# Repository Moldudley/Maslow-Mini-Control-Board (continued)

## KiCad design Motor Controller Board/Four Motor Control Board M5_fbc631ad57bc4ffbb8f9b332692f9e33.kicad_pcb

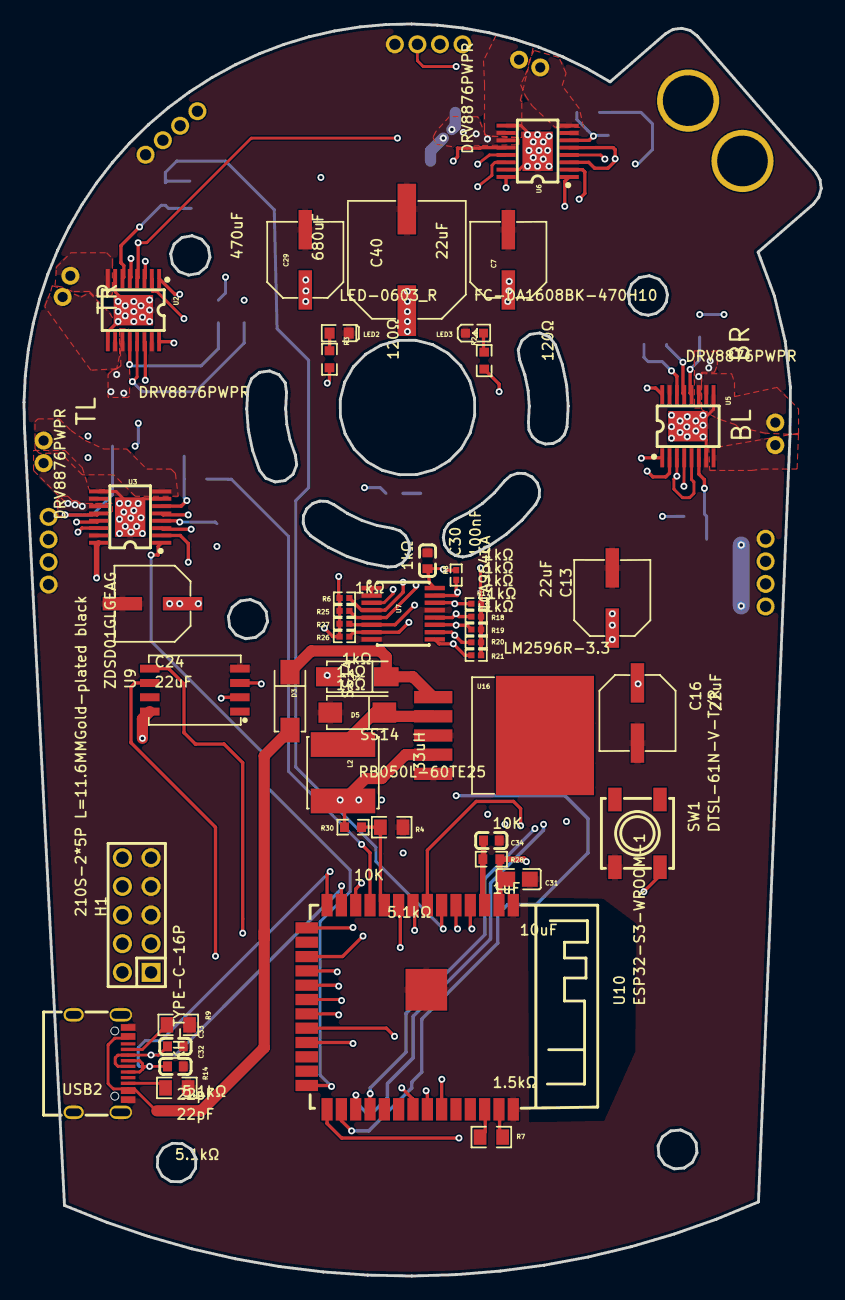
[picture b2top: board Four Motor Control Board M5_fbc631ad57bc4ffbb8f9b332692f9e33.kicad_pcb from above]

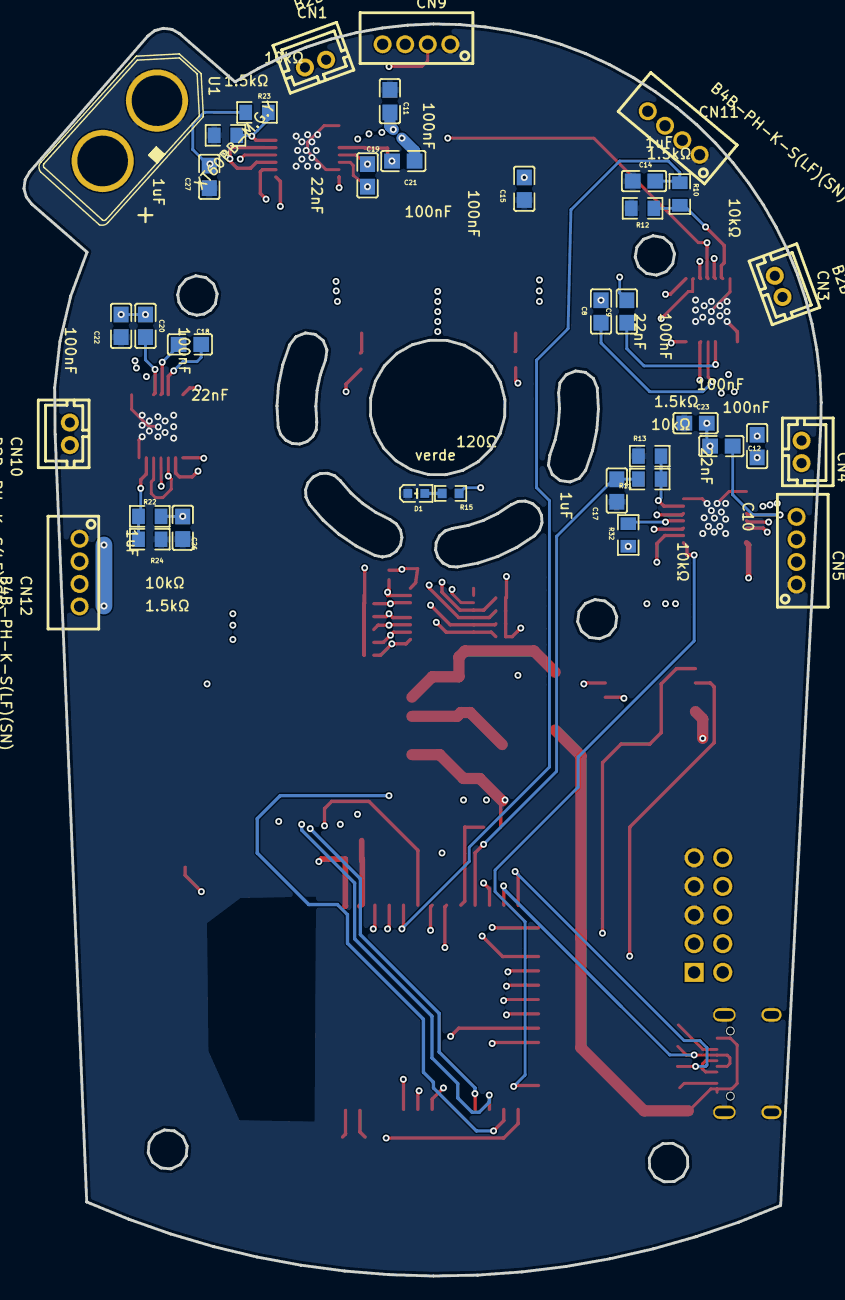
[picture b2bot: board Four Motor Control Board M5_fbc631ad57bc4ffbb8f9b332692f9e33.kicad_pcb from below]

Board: 4 copper layers, 70.7 x 111.0 mm, 82 parts (36 on the bottom side), 73 nets.

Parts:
C7, C13, C16, C24: 22uF; CAP-SMD_BD6.3-L6.6-W6.6-LS7.3-FD
C8, C10, C18, C19: 22nF; C0805
C9, C11, C12, C15, C20, C21, C22, C23: 100nF; C0805
C14, C17, C26, C27: 1uF; C0805
C29: 470uF; CAP-SMD_BD6.3-L6.6-W6.6-LS7.6-RD
C30: 100nF; C0603
C31: 10uF; C0805
C32, C33: 22pF; C0603
C34: 1uF; C0603
C40: 680uF; CAP-SMD_BD10.0-L10.3-W10.3-LS10.9-FD
CN1, CN3, CN4, CN10: B2B-PH-K-S(LF)(SN); CONN-TH_B2B-PH-K-S
CN5, CN9, CN11, CN12: B4B-PH-K-S(LF)(SN); CONN-TH_B4B-PH-K-S
D1: verde; LED0603-R-RD
D2, D3: SS14; SMA_L4.2-W2.6-LS5.3-RD
D5: RB050L-60TE25; SMA_L4.3-W2.7-LS5.1-RD
H1: 210S-2*5P L=11.6MMGold-plated black; HDR-TH_10P-P2.54-V-M-R2-C5-S2.54
L2: 33uH; IND-SMD_L6.0-W6.0
LED2: LED-0603_R; LED0603_RED
LED3: FC-DA1608BK-470H10; LED0603-RD
R1, R7, R12, R13, R24: 1.5kΩ; R0805
R2, R3, R15: 120Ω; R0603
R4, R9, R14: 5.1kΩ; R0805
R6, R8, R17, R18, R19, R20, R21, R25, R26, R27: 1kΩ; R0402
R10, R11, R22, R23, R32: 10kΩ; R0805
R28, R30: 10K; R0603
SW1: DTSL-61N-V-T/R; SW-SMD_4P-L6.2-W6.4-P4.00-LS7.2
U1: XT60PB-M.G.Y; CONN-TH_XT60PB-M
U2, U3, U5, U6: DRV8876PWPR; HTSSOP-16_L5.0-W4.4-P0.65-LS6.4-BL-EP
U7: TCA9546A; SOP-16_L5.0-W4.4-P0.65-LS6.4-BL
U9: ZDSD01GLGEAG; LGA-8_L6.0-W8.0-P1.27-BL
U10: ESP32-S3-WROOM-1
U16: LM2596R-3.3; TO-263-5_L10.2-W8.6-P1.70-LS14.4-TL
USB2: KH-TYPE-C-16P; USB-C-SMD_KH-TYPE-C-16P

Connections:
3V3: C29.1, C30.2, C31.2, CN5.4, CN9.4, CN11.4, CN12.4, L2.2, R6.2, R8.2, R15.2, R17.2, R18.2, R19.2, R20.2, R21.2, R25.2, R26.1, R27.2, R28.2, R30.2, R32.2, U2.3, U2.5, U2.16, U3.3, U3.5, U3.16, U5.3, U5.5, U5.16, U6.3, U6.5, U6.16, U7.3, U7.16, U9.8, U10.2, U16.4
ADCBL: C26.2, R22.1, U10.12
ADCBR: C27.2, R23.1, U10.7
ADCTL: C17.2, R11.1, U10.11
ADCTR: C14.2, R10.1, U10.6
AXISHEALTHLED: R3.2, U10.22
BLIN1: U5.1, U10.30
BLIN2: U5.2, U10.29
BLOUT1: CN10.2, U5.8
BLOUT2: CN10.1, U5.10
BOARDCOM1: H1.1, H1.3, U10.9
BOARDCOM2: H1.2, H1.4, U10.8
BOARDVERSION: R4.2, R30.1, U10.10
BOOT: SW1.2, U10.27
BRIN1: U6.1, U10.17
BRIN2: U6.2, U10.15
BROUT1: CN1.2, U6.8
BROUT2: CN1.1, U6.10
CLKV: U9.3, U10.20
D1_1: D1.1, R15.1
FAULT: R32.1, U2.4, U3.4, U5.4, U6.4, U10.33
GND: C7.2, C11.1, C13.2, C14.1, C15.1, C16.2, C17.1, C22.1, C23.1, C24.2, C26.1, C27.1, C29.2, C30.1, C31.1, C32.1, C33.1, C34.1, C40.2, CN5.1, CN9.1, CN11.1, CN12.1, D1.2, D5.2, H1.5, H1.7, H1.9, LED2.2, LED3.1, R1.1, R4.1, R9.1, R12.1, R13.1, R14.1, R24.1, SW1.4, U1.2, U2.7, U2.9, U2.15, U2.17, U3.7, U3.9, U3.15, U3.17, U5.7, U5.9, U5.15, U5.17, U6.7, U6.9, U6.15, U6.17, U7.1, U7.2, U7.8, U7.13, U9.4, U10.1, U10.40, U10.41, U16.3, U16.5, USB2.1, USB2.2, USB2.3, USB2.4, USB2.A1, USB2.A12, USB2.B1, USB2.B12
L2_1: D5.1, L2.1, U16.2
LED2_1: LED2.1, R3.1
LED3_2: LED3.2, R2.1
MCU_RST: C34.2, R28.1, U10.3
MISOV: U9.6, U10.21
MOSIV: U9.5, U10.19
SCL: R17.1, U7.14, U10.4
SCL0: CN9.2, R25.1, U7.5
SCL1: CN11.2, R26.2, U7.7
SCL2: CN5.2, R20.1, U7.10
SCL3: CN12.2, R18.1, U7.12
SDA: R8.1, U7.15, U10.5
SDA0: CN9.3, R6.1, U7.4
SDA1: CN11.3, R27.1, U7.6
SDA2: CN5.3, R21.1, U7.9
SDA3: CN12.3, R19.1, U7.11
SD_CS: U9.2, U10.18
TLIN1: U3.1, U10.26
TLIN2: U3.2, U10.23
TLOUT1: CN4.2, U3.8
TLOUT2: CN4.1, U3.10
TRIN1: U2.1, U10.35
TRIN2: U2.2, U10.34
TRINAMICRX: R7.1, U10.38
TRINAMICTX: R7.2, U10.39
TROUT1: CN3.2, U2.8
TROUT2: CN3.1, U2.10
U2_6: R10.2, R12.2, U2.6
U2_12: C9.2, U2.12
U2_13: C8.2, U2.13
U2_14: C8.1, U2.14
U3_6: R11.2, R13.2, U3.6
U3_12: C12.2, U3.12
U3_13: C10.2, U3.13
U3_14: C10.1, U3.14
U5_6: R22.2, R24.2, U5.6
U5_12: C20.2, U5.12
U5_13: C18.2, U5.13
U5_14: C18.1, U5.14
U6_6: R1.2, R23.2, U6.6
U6_12: C21.2, U6.12
U6_13: C19.2, U6.13
U6_14: C19.1, U6.14
U16_1: D2.1, D3.1, U16.1
USB2_A5: R9.2, USB2.A5
USB2_B5: R14.2, USB2.B5
USB5V: D3.2, USB2.A4, USB2.A9, USB2.B4, USB2.B9
USBD+: C32.2, U10.14, USB2.A6, USB2.B6
USBD-: C33.2, U10.13, USB2.A7, USB2.B7
VCC: C7.1, C9.1, C11.2, C12.1, C13.1, C15.2, C16.1, C20.1, C21.1, C22.2, C23.2, C24.1, C40.1, D2.2, H1.6, H1.8, H1.10, U1.1, U2.11, U3.11, U5.11, U6.11
WIFILED: R2.2, U10.28

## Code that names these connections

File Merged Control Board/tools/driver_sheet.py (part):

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 3. delete C30, the 100 nF EN cap.  The motor side's 1 uF (C134) survives as
    the single EN RC together with R28 and SW2, which now reset both MCUs.
    1 uF is the value Espressif's design guide asks for.
 4. the surviving BOARDCOM1/BOARDCOM2 labels at the ESP32 become hierarchical
    pins.  The crossover from the old H1 mating is preserved:
        driver BOARDCOM1 (IO39) -> BOARDCOM_B
        driver BOARDCOM2 (IO38) -> BOARDCOM_A
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    ("DRIVER SECTION", 4.0, True),
    ('Imported from "ProPrj_Driver Board to share_2026-08-01", except:', 1.8, False),
    ("  - H1 (2x5 board-to-board header) deleted; BOARDCOM1/2 at U12 are now hierarchical "
     "pins BOARDCOM_B / BOARDCOM_A", 1.8, False),
    ("  - MP2459 buck chain (U2, L3, D2, D6, C80, C81, R61-R63) deleted - the motor "
     "section's 3 A LM2596 now feeds both sections", 1.8, False),
    ("  - D7 kept, and now ORs this port's VBUS into the shared buck input VIN_BUCK", 1.8, False),
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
